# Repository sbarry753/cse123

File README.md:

# GuSynth – Ultra-Low-Latency Polyphonic Guitar Synth Pedal

GuSynth is a research + hardware project building a **real-time polyphonic guitar synth pedal** capable of transforming a guitar into other instruments with **ultra-low latency**.

The project combines:

- **Transient-guided neural note detection**
- **Polyphonic inference for guitar input**
- **Direct neural timbre transfer**
- **Embedded deployment on microcontroller hardware**
- **Analog tone shaping and post-processing**

The goal is a **standalone guitar pedal** that lets a guitarist play naturally while hearing the output as another instrument.

---

## Overview

Most pitch detection and guitar synthesis systems rely on longer analysis windows, which adds noticeable delay. GuSynth instead focuses on extracting useful information from the **earliest part of the note**, especially the pick attack, so the system can react quickly enough for live performance.

The project currently explores two connected ML stages:

1. **First neural network:** fast polyphonic note detection from very short windows
2. **Second neural network:** direct timbre transfer from guitar to another instrument

A harmonic LUT-based pipeline and analog processing stages support the overall system.

---

## Signal Path

This is the full signal path of the pedal, from instrument input through conversion, inference/synthesis, and output shaping.

---

## Overall Pedal / System Schematic

This diagram shows the higher-level pedal architecture and how the DSP / neural / synthesis stages connect together.

---

## 424 / Analog Circuit Reference

This section documents one of the analog reference directions used in the project for tone shaping / overdrive exploration.

---

## Core System Architecture

### 1. First Neural Network – Polyphonic Note Detection

The first model is designed to recognize notes from **very short guitar input windows**, with a strong focus on the **transient / pick attack** region.

It is intended to:

- detect note activity quickly
- work under polyphonic conditions
- provide a MIDI-style or note-based representation
- operate under strict latency constraints suitable for embedded systems

#### Audio Demo – First NN. Click images to view video.

**After (first NN output / note-detection-driven result):**

### 2. Second Neural Network – Timbre Transfer

The second model takes guitar input and transforms it toward the sound of another instrument.

Current work is focused on **guitar → piano-style transfer**, with the long-term goal of supporting more instruments and cleaner real-time conversion.

It is intended to:

- preserve performance timing and expression
- reshape the raw guitar waveform into a target timbre
- run in a streaming low-latency pipeline
- support eventual embedded deployment

#### Video Demo – Second NN. Click images to view video.

## Harmonic LUT Support Pipeline

Alongside the neural models, the project includes a harmonic fingerprint LUT approach used for analysis and refinement.

This system helps by:

- storing harmonic note templates
- comparing incoming spectra to expected note structure
- refining note hypotheses
- supporting interpretable DSP-guided analysis

Rather than treating the project as purely neural or purely classical DSP, GuSynth explores a **hybrid approach**.

---

## Embedded Hardware Target

The long-term target is a compact embedded pedal platform.

### Current embedded direction

- **Daisy Seed / Cortex-M7 class hardware**
- **48 kHz real-time audio**
- small-window streaming inference
- ADC / DAC audio pipeline
- analog front-end and output shaping

### Embedded constraints

- low total latency
- predictable real-time processing
- limited memory / compute budget
- models must be compact enough for sustained streaming

---

## Analog Processing

The pedal is not only digital / ML based. Analog stages are also important for:

- input conditioning
- gain staging
- distortion / overdrive
- EQ shaping
- reducing unpleasant artifacts in synthesized output

This is especially useful when blending guitar and synthetic instrument textures.

---

## Project Status

- ✅ First neural network prototype for transient-guided note detection
- ✅ Second neural network prototype for timbre transfer
- ✅ Harmonic LUT research pipeline
- ✅ System-level pedal architecture defined
- ⚠️ Embedded optimization still in progress
- ⚠️ More training data and refinement needed for cleaner output quality

---

## Repository Layout

- `Documentation/images/`  
  Diagrams, schematics, and system figures

- `Documentation/audio/`  
  WAV demos for model outputs

- `Documentation/video/`  
  Video demonstrations of the system

- `LUT - In Development/`  
  Harmonic fingerprint / template detection work

- `DAISY - In Development/`  
  Embedded hardware and firmware work

- `JUCE - In Development/`  
  Desktop or plugin prototyping

---

## Long-Term Goal

A standalone guitar pedal that:

- detects polyphonic playing with minimal delay
- converts guitar into the sound of other instruments
- runs on embedded hardware
- combines neural models, DSP, and analog circuitry
- remains responsive enough for real live performance

---

## Summary

GuSynth is a hybrid guitar-synthesis system exploring how far real-time note inference and timbre transfer can be pushed under embedded, performance-critical latency constraints.

It is not just a guitar effect — it is an attempt to turn the guitar into a **real-time expressive controller for other instruments**.

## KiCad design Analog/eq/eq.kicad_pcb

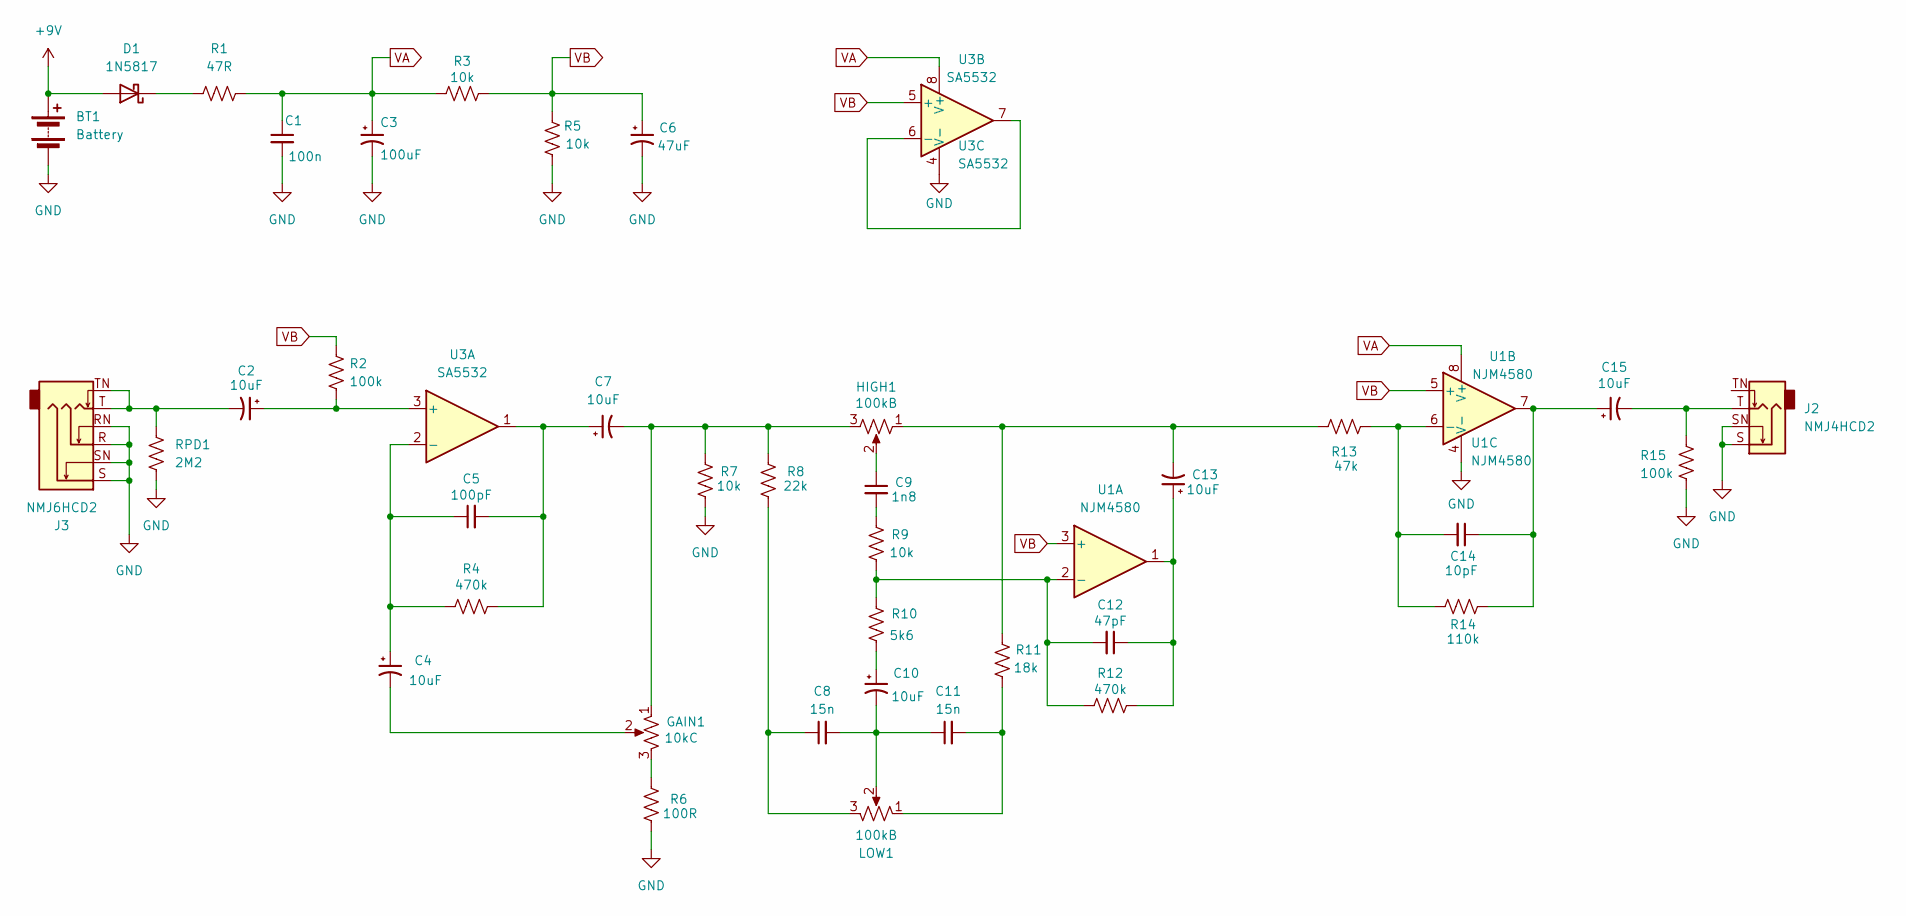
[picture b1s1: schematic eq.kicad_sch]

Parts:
BT1: Battery; PinHeader_1x02_P2.54mm_Vertical
C1: 100n; C_Rect_L7.0mm_W2.5mm_P5.00mm
C2, C4, C7, C10, C13, C15: 10uF; C_Radial_D5.0mm_H11.0mm_P2.00mm
C3: 100uF; C_Radial_D6.3mm_H11.0mm_P2.50mm
C5: 100pF; C_Rect_L7.0mm_W2.5mm_P5.00mm
C6: 47uF; C_Radial_D5.0mm_H11.0mm_P2.00mm
C8, C11: 15n; C_Rect_L7.2mm_W2.5mm_P5.00mm
C9: 1n8; C_Rect_L7.2mm_W2.5mm_P5.00mm
C12: 47pF; C_Rect_L7.0mm_W2.5mm_P5.00mm
C14: 10pF; C_Rect_L7.0mm_W2.5mm_P5.00mm
D1: 1N5817; D_DO-41_SOD81_P10.16mm_Horizontal
GAIN1: 10kC; Potentiometer_Omeg_PC16BU_Vertical
HIGH1: 100kB; Potentiometer_Omeg_PC16BU_Vertical
J2: NMJ4HCD2; Jack_6.35mm_Neutrik_NMJ4HCD2_Horizontal
J3: NMJ6HCD2; Jack_6.35mm_Neutrik_NMJ6HCD2_Horizontal
LOW1: 100kB; Potentiometer_Omeg_PC16BU_Vertical
R1: 47R; R_Axial_DIN0207_L6.3mm_D2.5mm_P10.16mm_Horizontal
R2, R15: 100k; R_Axial_DIN0207_L6.3mm_D2.5mm_P10.16mm_Horizontal
R3, R5, R7, R9: 10k; R_Axial_DIN0207_L6.3mm_D2.5mm_P10.16mm_Horizontal
R4, R12: 470k; R_Axial_DIN0207_L6.3mm_D2.5mm_P10.16mm_Horizontal
R6: 100R; R_Axial_DIN0207_L6.3mm_D2.5mm_P10.16mm_Horizontal
R8: 22k; R_Axial_DIN0207_L6.3mm_D2.5mm_P10.16mm_Horizontal
R10: 5k6; R_Axial_DIN0207_L6.3mm_D2.5mm_P10.16mm_Horizontal
R11: 18k; R_Axial_DIN0207_L6.3mm_D2.5mm_P10.16mm_Horizontal
R13: 47k; R_Axial_DIN0207_L6.3mm_D2.5mm_P10.16mm_Horizontal
R14: 110k; R_Axial_DIN0207_L6.3mm_D2.5mm_P10.16mm_Horizontal
RPD1: 2M2; R_Axial_DIN0207_L6.3mm_D2.5mm_P10.16mm_Horizontal
U1: NJM4580; DIP-8_W7.62mm_LongPads
U3: SA5532; DIP-8_W7.62mm_LongPads

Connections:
+9V: BT1.1 (+), D1.2 (A)
GND: BT1.2 (-), C1.2, C3.2, C6.2, J2.S, J2.SN, J3.R, J3.RN, J3.S, J3.SN, R5.2, R6.2, R7.2, R15.2, RPD1.2, U1.4 (V-), U3.4 (V-)
unnamed: C2.2, J3.T, J3.TN, RPD1.1
unnamed: C4.2, GAIN1.2
unnamed: C5.2, C7.1, R4.2, U3.1
unnamed: C7.2, GAIN1.1, HIGH1.3, R7.1, R8.1
unnamed: C8.1, LOW1.3, R8.2
unnamed: C9.1, HIGH1.2
unnamed: C9.2, R9.1
unnamed: C10.1, R10.2
unnamed: C8.2, C10.2, C11.1, LOW1.2
unnamed: C11.2, LOW1.1, R11.2
unnamed: C12.1, C13.1, R12.1, U1.1
unnamed: C13.2, HIGH1.1, R11.1, R13.2
unnamed: C14.1, C15.1, R14.1, U1.7
unnamed: C15.2, J2.T, R15.1
unnamed: D1.1 (K), R1.1
unnamed: GAIN1.3, R6.1
unnamed: C12.2, R9.2, R10.1, R12.2, U1.2 (-)
unnamed: C14.2, R13.1, R14.2, U1.6 (-)
unnamed: C2.1, R2.2, U3.3 (+)
unnamed: C4.1, C5.1, R4.1, U3.2 (-)
unnamed: U3.6 (-), U3.7
VA: C1.1, C3.1, R1.2, R3.1, U1.8 (V+), U3.8 (V+)
VB: C6.1, R2.1, R3.2, R5.1, U1.3 (+), U1.5 (+), U3.5 (+)

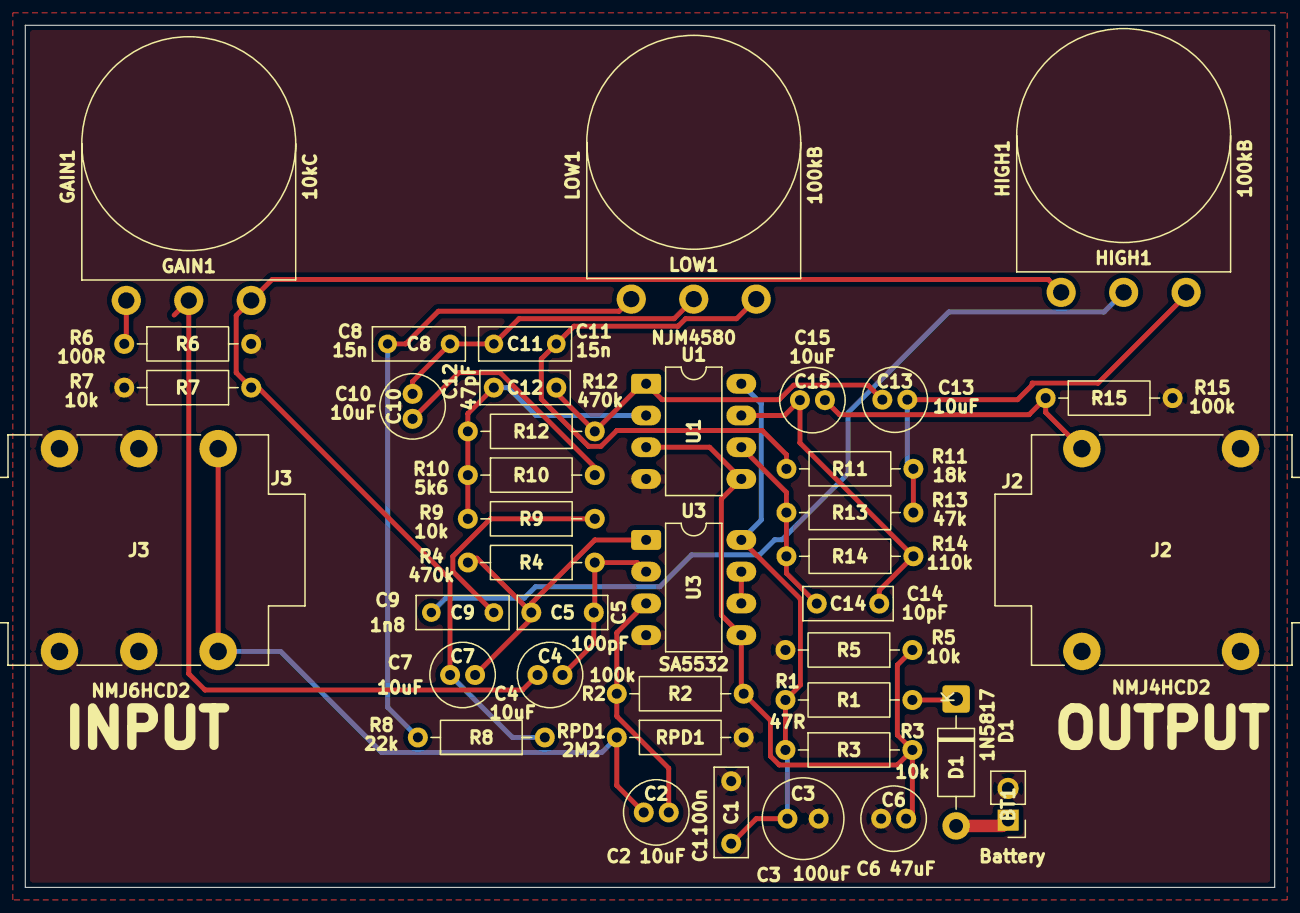
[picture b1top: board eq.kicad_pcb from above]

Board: 2 copper layers, 100.0 x 69.0 mm, 40 parts (0 on the bottom side), 25 nets.

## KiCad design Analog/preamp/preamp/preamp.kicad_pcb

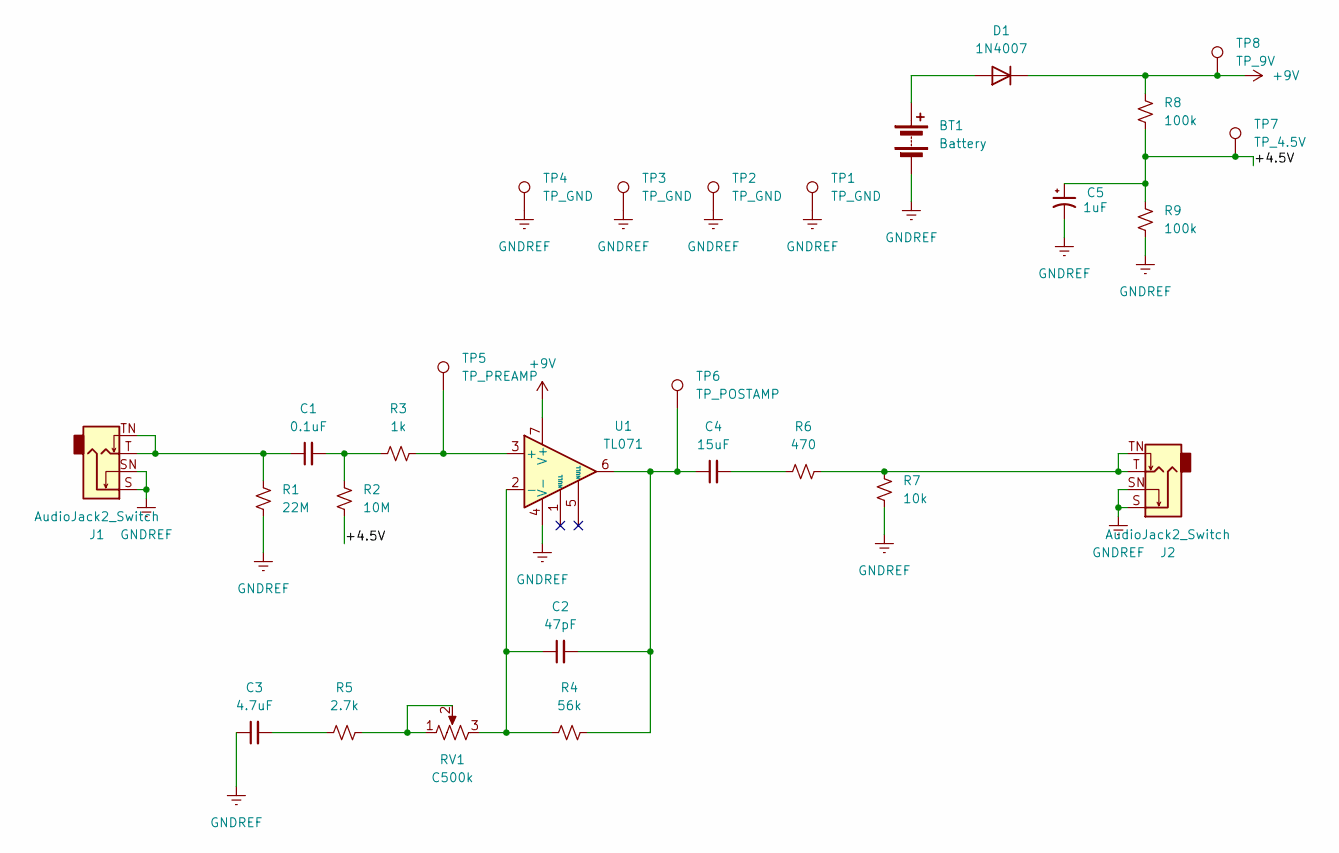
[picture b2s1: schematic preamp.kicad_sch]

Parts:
BT1: Battery; PinSocket_1x02_P2.54mm_Vertical
C1: 0.1uF; CP_Radial_D8.0mm_P3.80mm
C2: 47pF; CP_Radial_D8.0mm_P3.80mm
C3: 4.7uF; CP_Radial_D8.0mm_P3.80mm
C4: 15uF; CP_Radial_D8.0mm_P3.80mm
C5: 1uF; CP_Radial_D8.0mm_P3.80mm
D1: 1N4007; D_DO-41_SOD81_P10.16mm_Horizontal
J1, J2: AudioJack2_Switch; Jack_6.35mm_Neutrik_NMJ4HCD2_Horizontal
R1: 22M; R_Axial_DIN0414_L11.9mm_D4.5mm_P15.24mm_Horizontal
R2: 10M; R_Axial_DIN0414_L11.9mm_D4.5mm_P15.24mm_Horizontal
R3: 1k; R_Axial_DIN0414_L11.9mm_D4.5mm_P15.24mm_Horizontal
R4: 56k; R_Axial_DIN0414_L11.9mm_D4.5mm_P15.24mm_Horizontal
R5: 2.7k; R_Axial_DIN0414_L11.9mm_D4.5mm_P15.24mm_Horizontal
R6: 470; R_Axial_DIN0414_L11.9mm_D4.5mm_P15.24mm_Horizontal
R7: 10k; R_Axial_DIN0414_L11.9mm_D4.5mm_P15.24mm_Horizontal
R8, R9: 100k; R_Axial_DIN0414_L11.9mm_D4.5mm_P15.24mm_Horizontal
RV1: C500k; Potentiometer_Alpha_RD901F-40-00D_Single_Vertical
TP1, TP2, TP3, TP4: TP_GND; TestPoint_Loop_D3.50mm_Drill0.9mm_Beaded
TP5: TP_PREAMP; TestPoint_Loop_D3.50mm_Drill0.9mm_Beaded
TP6: TP_POSTAMP; TestPoint_Loop_D3.50mm_Drill0.9mm_Beaded
TP7: TP_4.5V; TestPoint_Loop_D3.50mm_Drill0.9mm_Beaded
TP8: TP_9V
U1: TL071; DIP-8_W7.62mm_LongPads

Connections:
+9V: D1.1 (K), R8.1, TP8.1, U1.7 (V+)
/+4.5V: C5.1, R2.2, R8.2, R9.1, TP7.1 (1_1)
GNDREF: BT1.2 (-), C3.1, C5.2, J1.S, J1.SN, J2.S, J2.SN, R1.2, R7.2, R9.2, TP1.1 (1_1), TP2.1 (1_1), TP3.1 (1_1), TP4.1 (1_1), U1.4 (V-)
unnamed: BT1.1 (+), D1.2 (A)
unnamed: C1.1, J1.T, J1.TN, R1.1
unnamed: C1.2, R2.1, R3.1
unnamed: C2.2, C4.1, R4.2, TP6.1 (1_1), U1.6
unnamed: C3.2, R5.1
unnamed: C4.2, R6.1
unnamed: J2.T, J2.TN, R6.2, R7.1
unnamed: R5.2, RV1.1, RV1.2
unnamed: R3.2, TP5.1 (1_1), U1.3 (+)
unnamed: C2.1, R4.1, RV1.3, U1.2 (-)

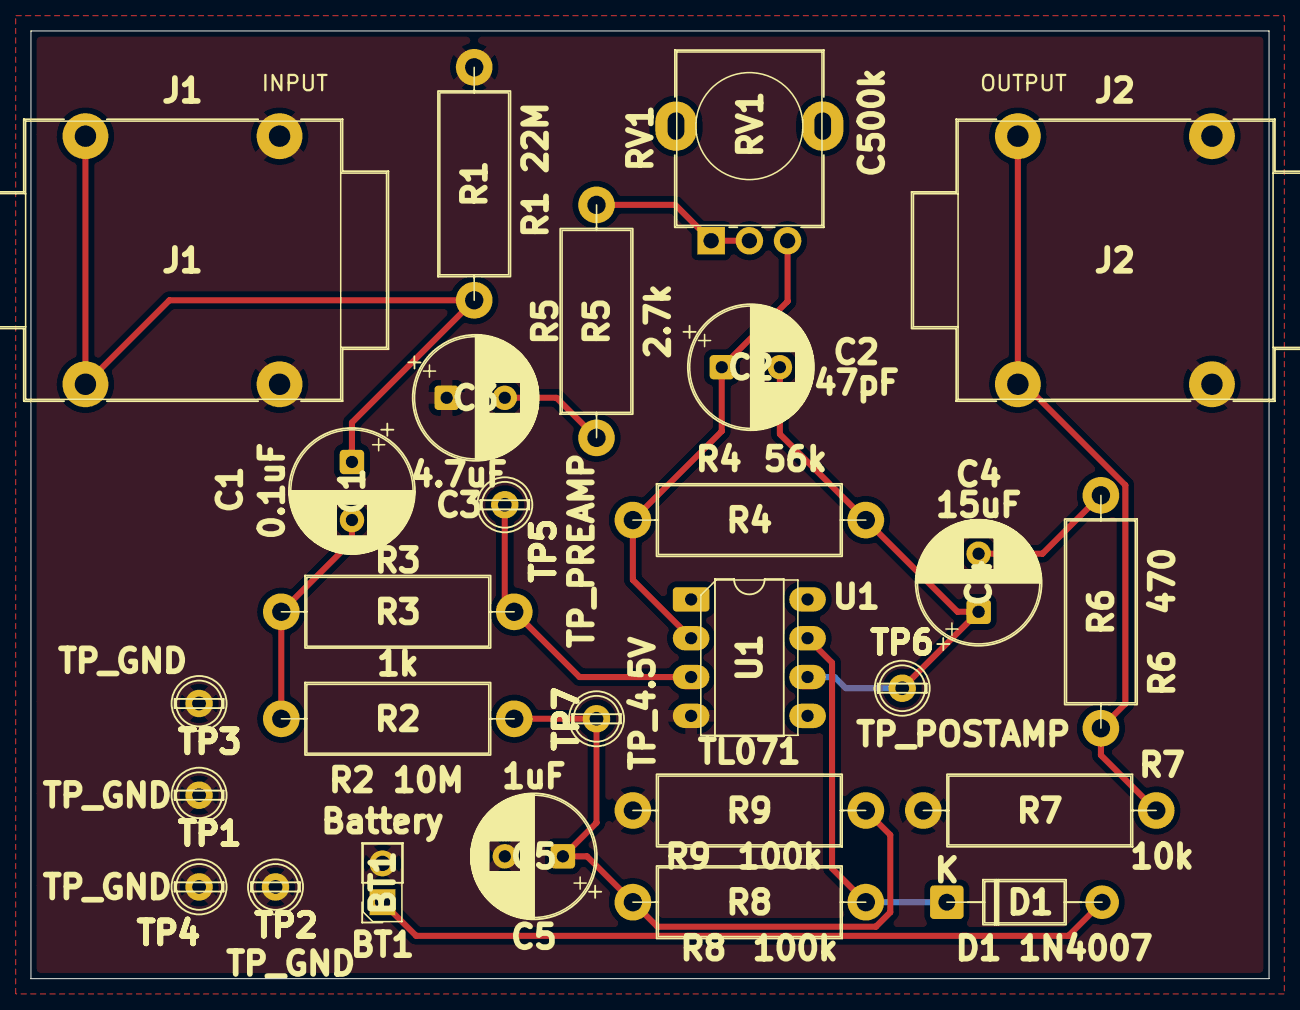
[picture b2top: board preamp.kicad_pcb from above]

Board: 2 copper layers, 81.0 x 62.0 mm, 27 parts (0 on the bottom side), 13 nets.

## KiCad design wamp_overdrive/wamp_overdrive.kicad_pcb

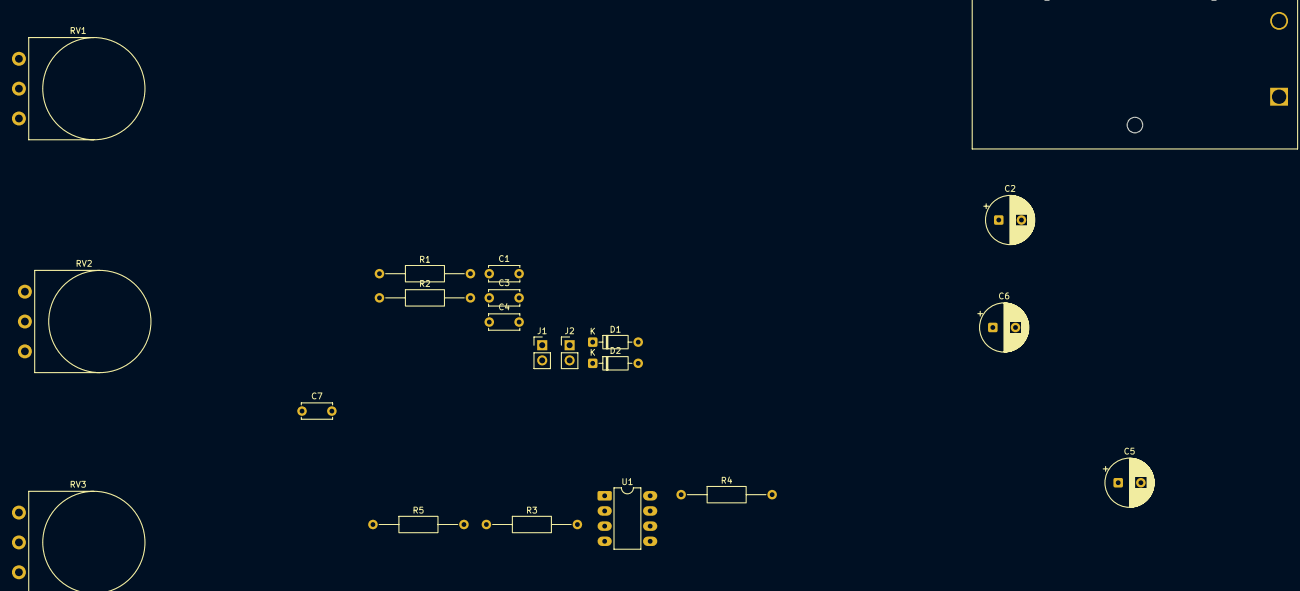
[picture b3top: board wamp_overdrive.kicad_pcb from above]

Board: 2 copper layers, 21 parts (0 on the bottom side), 11 nets, no tracks yet.

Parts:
BT1: Battery; BatteryHolder_Eagle_12BH611-GR
C1: 470nF; C_Disc_D5.0mm_W2.5mm_P5.00mm
C2, C6: 47uF; CP_Radial_D8.0mm_P3.80mm
C3: 220nF; C_Disc_D5.0mm_W2.5mm_P5.00mm
C4: 100pF; C_Disc_D5.0mm_W2.5mm_P5.00mm
C5: 1uF; CP_Radial_D8.0mm_P3.80mm
C7: 22nF; C_Disc_D5.0mm_W2.5mm_P5.00mm
D1, D2: 1N4148; D_DO-35_SOD27_P7.62mm_Horizontal
J1, J2: AudioJack2; PinHeader_1x02_P2.54mm_Vertical
R1, R2, R4: 10k; R_Axial_DIN0207_L6.3mm_D2.5mm_P15.24mm_Horizontal
R3: 1M; R_Axial_DIN0207_L6.3mm_D2.5mm_P15.24mm_Horizontal
R5: 1k; R_Axial_DIN0207_L6.3mm_D2.5mm_P15.24mm_Horizontal
RV1: 500k; Potentiometer_Omeg_PC16BU_Vertical
RV2: 10k; Potentiometer_Omeg_PC16BU_Vertical
RV3: 100k; Potentiometer_Omeg_PC16BU_Vertical
U1: TL082; DIP-8_W7.62mm_LongPads

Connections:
+9V: BT1.1 (+), C6.1, R4.1, U1.8 (V+)
GND: BT1.2 (-), C2.2, C3.2, C6.2, C7.1, R2.2, RV3.3, U1.4 (V-)
unnamed: C1.1, R1.2
unnamed: C2.1, R2.1, R3.1, R4.2
unnamed: C3.1, R5.2
unnamed: C5.1, RV2.3
unnamed: C7.2, RV2.2
unnamed: C4.1, D1.2 (A), D2.1 (K), R5.1, RV1.3, U1.2 (-)
unnamed: C4.2, C5.2, D1.1 (K), D2.2 (A), RV1.1, RV1.2, U1.1
unnamed: RV2.1, RV3.1
unnamed: C1.2, R3.2, U1.3 (+)

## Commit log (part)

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2026-02-22 So this was a learning process
2026-02-22 Experimentation moved to specified folder
2026-02-23 onset please work
2026-02-23 ideal note computation
2026-02-23 what am I doingh here
2026-02-23 dont need these my bad
2026-02-23 Nothing works as expected
2026-02-23 OMP flag
2026-02-23 new samples
2026-02-23 What an unproductive day
2026-02-23 ehhhh little better
2026-02-23 woohoo 40% accuracy model. THATS TRASH!
2026-02-23 need to revert
2026-02-23 this is a bad idea and doesnt work
2026-02-23 restructure+prototype dataset script
2026-02-23 made the wampler overdrive pedal schematic in kicad
2026-02-23 this should detect trail off
2026-02-24 human timing needs uopdate
2026-02-24 UGH I did the ntoe math wrong, fix next commit
2026-02-24 Beautiful, builds dataset PERFECTLY
2026-02-24 Neural net prototype code phase 1 on 512 training size
2026-02-24 Fix hold head learning: label hold-positive on transient windows
2026-02-24 this is a little better but still bad
2026-02-24 This is a good spot but it REALLY needs data to train on
2026-02-24 more data woohoo!
2026-02-24 Dataset update
2026-02-24 forgot resume
2026-02-24 AHHHH 2 more strings left
2026-02-24 Val debug
2026-02-24 Very promising. over 70% accuracy for top 3 notes
2026-02-24 I sleep now, this is working, continue training tmr
2026-02-24 Fuzz effect (hardcoded)
2026-02-24 Updated organization
2026-02-24 update gitignore
2026-02-24 Added wavefolding and tone
2026-02-24 Removed chatgpt garbage that didnt work. Learned about Cross Entropy
2026-02-25 56% accuracy as top 1 note, 78% as top 3
2026-02-25 ONE MORE STRING TO GOOOOO
2026-02-25 benchmarking code, need to run experiments
2026-02-25 Special effects (#57)
    * New tree for special_effects
    * Updated special effects feature
    * Updated Special_effects dir
    * Fuzz effect (hardcoded)
    * Updated organization
    * update gitignore
2026-02-25 corrected note to midi convention
2026-02-25 negatives generator
2026-02-25 negatives werent negativing
2026-02-26 Dataset with true negatives
2026-02-26 Updated main.cpp and effects
2026-02-26 agc.h
2026-02-26 finished benchmarking effects, will stress-test with matmul
2026-02-26 string classifier
2026-02-26 Fft and NN combined together!!!
2026-02-26 Add files via upload
    Pinout Reference for Daisy Seed STM32H750 Microcontroller
2026-02-27 Updated local and prep for embedded integration
2026-02-27 Very very close
2026-02-28 Adding Daisy Seed Pinout Diagram
2026-03-01 Python Synth
2026-03-02 some mm benchmarking...
2026-03-03 we trying
2026-03-04 Create script placeholder so i can make new dir
2026-03-05 Not FFT or comb but was seeing if NN worked and it does hjust like trash
2026-03-05 Desktop C++ sim
2026-03-07 finished daisy matmul stress test
2026-03-07 cont. benchmarking daisy
2026-03-07 updated daisy README to outline flashing steps
2026-03-07 init benchmarking code
2026-03-07 Delete Demo Materials
    i messed up this was supposed to be a directory
2026-03-07 Rough draft demo script
    Added a demo script for the polyphonic synth pedal presentation, including setup instructions, an introduction, need statement, system overview, and live demonstration details.
2026-03-10 profiled nn and converted nn to tflm
2026-03-10 Final net update
2026-03-11 added in-progress design doc PDF
2026-03-11 Add Status Report 4 with project updates and plans
2026-03-11 Create Status Report 5 with project updates
    Added Status Report 5 detailing project progress, goals, and testing plans.
2026-03-11 Create Status Report 6 with project updates
    Added Status Report 6 detailing project updates, goals, and testing plans.
2026-03-11 Add need statement for guitar-controlled synthesizers
2026-03-11 Add goal statement for guitar synth pedal project
2026-03-11 Add design objectives for guitar note detection
    Document design objectives for polyphonic note detection in guitar pedals.
2026-03-11 Add personas for guitar players and synth effects
2026-03-11 uploading current design schematic
    TA wants 5 bare minimum requirements pushed to git
2026-03-11 skeleton for end-of-quarter design document draft
2026-03-12 rough draft of demo slide panel
    top left corner diagram
2026-03-12 Updated special_effects
2026-03-12 nets!!!
2026-03-12 better n
2026-03-12 88% accuracy top 1 notes
2026-03-12 New NN + Pitch Detect
2026-03-12 new exporter
2026-03-13 Final Monophonic NN
2026-03-13 Adding special_effects developments
2026-03-13 Nn daisy tflite (#80)
    * we trying
    * Not FFT or comb but was seeing if NN worked and it does hjust like trash
    * Desktop C++ sim
    * profiled nn and converted nn to tflm
    ---------
2026-03-13 Beginning NN guitar changer
2026-03-13 woop
2026-03-13 Train on desktop
2026-03-13 Piano Resynth
2026-03-13 start of 424 schematic; no component values yet
2026-03-13 updated the wampler overdrive pedal schematic
2026-03-13 updated gitignore and overdrive schematic and added a pdf of the new schematic
2026-03-13 adding aesthetic prototype to Documentation
2026-03-14 Updating Pull Request
2026-03-14 Special effects (#85)
    * New tree for special_effects
    * Updated special effects feature
    * Updated Special_effects dir
    * Fuzz effect (hardcoded)
    * Updated organization
    * update gitignore
2026-03-14 completed 424 kicad schematic
2026-03-14 added notes
2026-03-14 424 schematic pdf
2026-03-14 doc images import from overleaf
2026-03-15 import design document .tex from overleaf
2026-03-15 remove latency doc info; moving to wiki
2026-03-15 needs more data
2026-03-15 Delete Demo_Materials/demoSlide.pptx
    not using pptx anymore, refer to canva
2026-03-16 data; di song fragments
2026-03-17 dataset adding chords, intervals, random notes
2026-03-18 documenting final version
2026-03-23 more riffs
2026-03-23 morw
2026-03-23 Reaper hates me
2026-03-23 IT WORKS
2026-03-23 Dataest updat
2026-03-23 New model
2026-03-23 more
2026-03-23 B note
2026-03-23 change
2026-03-23 qhoop
2026-03-23 New havy hammer NN
2026-03-23 Better reward
2026-03-23 export.py
2026-03-23 High notes
2026-03-23 noise reducer
2026-03-23 high fix
2026-03-23 Epoch
2026-03-23 best
2026-03-23 C notes
2026-03-23 Fional commit for quarter
2026-03-23 Better model
2026-03-27 wroking model
2026-03-27 ReadmeUpdate
2026-03-27 Fix image and video source paths in README
    Updated image and video source paths in README.md to remove leading './'.
2026-03-27 finished?
2026-03-27 Update demo section titles in README
2026-03-30 Dataset re write
2026-03-30 Add README.md for demo materials directory
2026-03-30 added readme
2026-03-30 Guitar addititons
2026-03-30 Zion guitar
2026-03-31 Updating special_effects to deprecated, and creating MidiScript dir
2026-03-31 init temporal nn tflite
2026-04-02 export temporal model in raw C for baseline
2026-04-03 some baseline experiments
2026-04-07 Created midi_to_wav.py
2026-04-08 A notes
2026-04-08 B notes
2026-04-08 Riffage
2026-04-14 add ref examples ready for testing
2026-04-15 Rework to act like old revision
    UNTESTED
2026-04-20 ignore
2026-04-22 reorganized pedal schematics into Analog folder and adding analog weekly report #1
2026-04-22 Organizational & Added circular_buffer
2026-04-22 tflm timbre benchmark
2026-04-22 removed tracking of generated model headers
2026-04-22 adding analog weekly report #2
2026-04-22 compressed photo
2026-04-24 Renamed software to deprecated_software to tidy up old files we don't need & added upgrade folder with README.md with our current upgrade approach
2026-04-27 No auto kicad backups PLEASE
2026-04-27 preamp pcb made
2026-04-28 eq schematic made and parts assigned
2026-04-28 EQ pcb started and Analog file re-org
2026-04-29 EQ pcb done
2026-04-29 update gitignore for KiCAD
2026-04-30 audio passes through feather, not using FreeRTOS or anything
2026-05-02 update gitignore for Eclipse
2026-05-02 started compression and sustainer pedal pcb
2026-05-04 correction for cli debug command
2026-05-04 clean up audio passthrough i2c delay code
2026-05-05 audio passthrough with freeRTOS
2026-05-05 finally pushed some of the nn code
2026-05-05 Fixed NN, better highh notes, and sounds like a piano
2026-05-06 onnx
2026-05-06 model best
2026-05-06 re add .gitignore contents
    Added various Eclipse-related files and directories to .gitignore to prevent them from being tracked.
2026-05-06 clean but less piano sounding
2026-05-06 Feather audio passthrough with FreeRTOS (#170)
    * audio passes through feather, not using FreeRTOS or anything
    * correction for cli debug command
    * clean up audio passthrough i2c delay code
    * audio passthrough with freeRTOS
2026-05-07 init student nn
2026-05-07 poster rough draft
2026-05-08 put model on max, failing known-answer test
2026-05-09 fixed known-sample test
2026-05-09 init distillation
2026-05-09 distilled model sounds too guitar-like
2026-05-10 trying unet
2026-05-10 Update circular buffer README
2026-05-10 Add FreeRTOS audio passthru with circular buffer integration
2026-05-11 Python for testing jetson live playback
2026-05-11 feat: Add aliases and folders for contribution metrics
2026-05-13 max nn stuff
2026-05-13 fixed battery trace
2026-05-13 hope this works
2026-05-13 edit
2026-05-13 edits
2026-05-13 fp fix
2026-05-13 jetson tensorRT
2026-05-13 desperate attempts to improve latency
2026-05-13 best model
2026-05-13 add wav support
2026-05-14 surely this works
2026-05-14 trying something else
2026-05-16 trying better full model to remove distortion
2026-05-19 added debug script
2026-05-20 fixed OLA, much less distortio
2026-05-21 updated realtime_onnx_orin with improved OLA
2026-05-21 model with 2048 frame size/TCN/TransientCorrection for orin
2026-05-21 fixed import
2026-05-21 exported updated model to onnx
2026-05-21 added CL frame size arg
2026-05-21 added hop size
2026-05-21 added onnx model with 1024 frame sie size
2026-05-21 fixed 1024 model
2026-05-21 added model with 512 frame size
2026-05-21 added model with 768 frame size
2026-05-21 final 768 model
2026-06-08 step file
2026-06-08 eq stl
2026-06-09 top down view of GuSynth
2026-06-09 updated README.md in TIMBRE NET + cleaned up directory
